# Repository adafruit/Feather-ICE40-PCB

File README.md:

# Feather ICE40 #
This is a Feather board featuring an ICE40 FPGA. It can either be used as a soft core CPU or for dedicated logic.

## Contributing ##
Please note that this project is released with a [Contributor Code of Conduct](CODE_OF_CONDUCT.md). By participating in this project you agree to abide by its terms.

### Setup ###
Components and footprints for PCB parts are not included in this repository. Instead, checkout the [adafruit/kicad-libs](https://github.com/adafruit/kicad-libs) repository in the same directory that this repository is checked out in. All part definitions should be relative so that they will load correctly.

### Pull requests ###
For fixes please submit a pull request to the original repository.

### Derivatives ###
If developing your own version of the Feather ICE40 please remove all Chickadee Tech and Adafruit trademarks and follow the [CC-BY license](LICENSE). While not required, please consider open sourcing your modifications so others can learn from your improvements.

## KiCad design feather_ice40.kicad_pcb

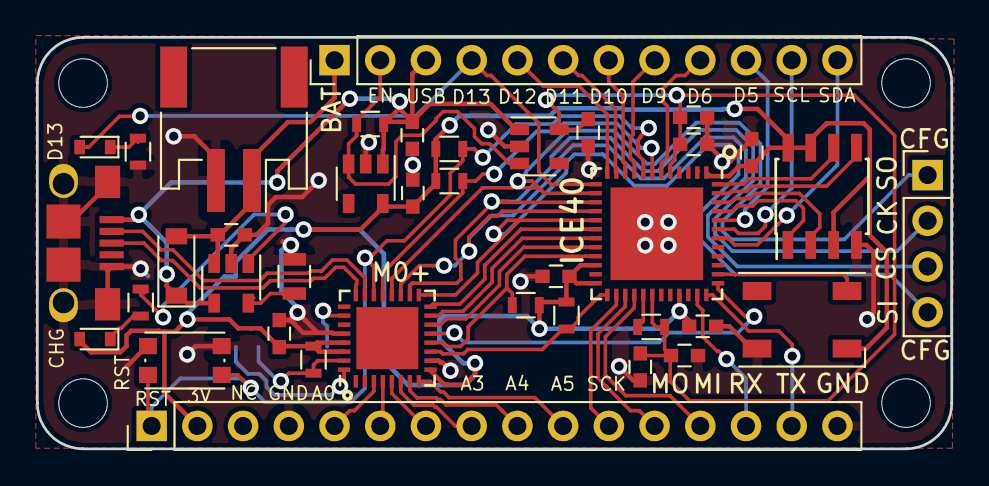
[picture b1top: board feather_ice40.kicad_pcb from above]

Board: 2 copper layers, 50.8 x 22.9 mm, 43 parts (1 on the bottom side), 53 nets.

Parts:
C1, C2, C4, C5, C8: 0.1uF; C_0603
C6, C14, C16, C19, C20: 10uF; C_0603
C7, C18: 1uF; C_0603
D1: MBR120; D_SOD-123
D2: Yellow; D_0603
D3: Red; D_0603
D4: Neopixel_THT; LED_WS2812B-PLCC4
J1: USB_OTG; Mini-USB-B-OshPark
J2: CONN_01X02; JST_PH_S2B-PH-SM4-TB_02x2.00mm_Angled
J3, J4, J5, J6: CONN_01X01; MountingHole_2.7mm_M2.5
J7: CONN_02X05; Pin_Header_Straight_2x05_Pitch1.27mm_SMD
J8: Conn_01x04; Pin_Header_Straight_1x04_Pitch2.54mm
J9: FeatherBottom; Pin_Header_Straight_1x16_Pitch2.54mm
J10: FeatherTop; Pin_Header_Straight_1x12_Pitch2.54mm
R1, R3: 10k; R_0603
R2: 100; R_0603
R4: 100k; R_0603
R5, R8, R10: 1k; R_0603
R6, R7: 4.7k; R_0603
R9: 10k; R_0805
SW1: SW_SPST; SW_SPST_KMR2
U1: ICE40UP5K-SG48; QFN-48-1EP_7x7mm_Pitch0.5mm
U2: IS25LPXXX; SOIC-8_3.9x4.9mm_Pitch1.27mm
U3: SPX3819M5-L-3-3/TR; SOT-23-5
U4: SPX3819M5-L-1-2/TR; SOT-23-5
U5: SAMD21E; QFN-32-1EP_5x5mm_Pitch0.5mm
U6: MCP73831; SOT-23-5

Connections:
+1V2: C5.1, C6.1, C7.1, C8.1, C16.1, R2.1, U1.5, U1.30, U4.5
+3V3: C1.1, C2.1, C4.1, C14.1, C18.2, D2.2, D4.3, J7.1, J9.2, R1.1, R3.1, R6.1, R7.1, R10.1, U1.1, U1.22, U1.24, U1.33, U2.3, U2.7, U2.8, U3.5, U5.9, U5.29, U5.30
+5V: C19.1, D1.1, J1.1, J10.3, R4.1, U3.1, U4.1, U6.4
+BATT: C20.1, D1.2, J2.1, J10.1, U6.3
/A0: J9.5, U5.3
/A1: J9.6, U5.4
/A2: J9.7, U5.5
/A3: J9.8, U5.6
/A4: J9.9, U5.7
/A5: J9.10, U5.8
/CHARGE: R5.2, U6.1
/D5: J10.10, U1.44
/D6: J10.9, U1.6
/D9: J10.8, U1.9
/D10: J10.7, U1.10
/D11: J10.6, U1.11
/D12: J10.5, U1.12
/D13: D3.2, J10.4, U1.13
/EN: J10.2, R4.2, U3.3, U4.3
/GCLK4: U1.37, U5.13
/GCLK5: U1.20, U5.14
/M0RX: U1.18, U5.16
/M0TX: U1.19, U5.15
/M0_RST: J7.10, U5.26
/M0_SWCLK: J7.4, R10.2, U5.31
/M0_SWDIO: J7.2, U5.32
/NEOPIX: D4.4, U1.38
/USB_D+: J1.3, U5.24
/USB_D-: J1.2, U5.23
/cdone: R3.2, U1.7, U5.21
/configMISO: J8.1, U1.14, U5.20
/configMOSI: J8.4, U1.17, U5.17
/configSCK: J8.2, U1.15, U5.18
/configSS: J8.3, U1.16, U5.19
/flashMISO: U1.46, U2.2
/flashMOSI: U1.47, U2.5
/flashSCK: U1.48, U2.6
/flashSS: U1.45, U2.1
/iceMISO: J9.13, U1.28
/iceMOSI: J9.12, U1.27
/iceRX: J9.14, U1.35
/iceReset: J9.1, R1.2, SW1.2, U1.8, U5.22
/iceSCK: J9.11, U1.26
/iceSCL: J10.11, U1.43
/iceSDA: J10.12, U1.42
/iceTX: J9.15, U1.36
/sharedSCL: R6.2, U1.21, U5.12
/sharedSDA: R7.2, U1.25, U5.11
GND: C1.2, C2.2, C4.2, C5.2, C6.2, C7.2, C8.2, C14.2, C16.2, C18.1, C19.2, C20.2, D4.2, J1.5, J1.6, J2.2, J7.3, J7.5, J9.4, J9.16, R8.2, R9.2, SW1.1, U1.49, U2.4, U3.2, U4.2, U5.10, U5.28, U6.2
unnamed: D2.1, R5.1
unnamed: D3.1, R8.1
unnamed: R2.2, U1.29
unnamed: R9.1, U6.5

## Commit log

2017-09-10 Original FPGA design with BGA ICE40 8k.
2017-09-11 Fully routed. Needs silk cleanup.
2017-09-11 Silkscreen polish.
